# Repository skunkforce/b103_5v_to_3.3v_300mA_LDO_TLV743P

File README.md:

# edgy_board number b123
This design is part of the [edgy board project](https://github.com/skunkforce/edgy_boards). It provides a 3.3v 300mA LDO

# getting started
This repository uses submodules. After cloning use the command 

```$ git submodule update --init --recursive```

to pull the submodules before opening the project with kicad. 

# Tests
Tests can be found in [TESTS.md](TESTS.md)

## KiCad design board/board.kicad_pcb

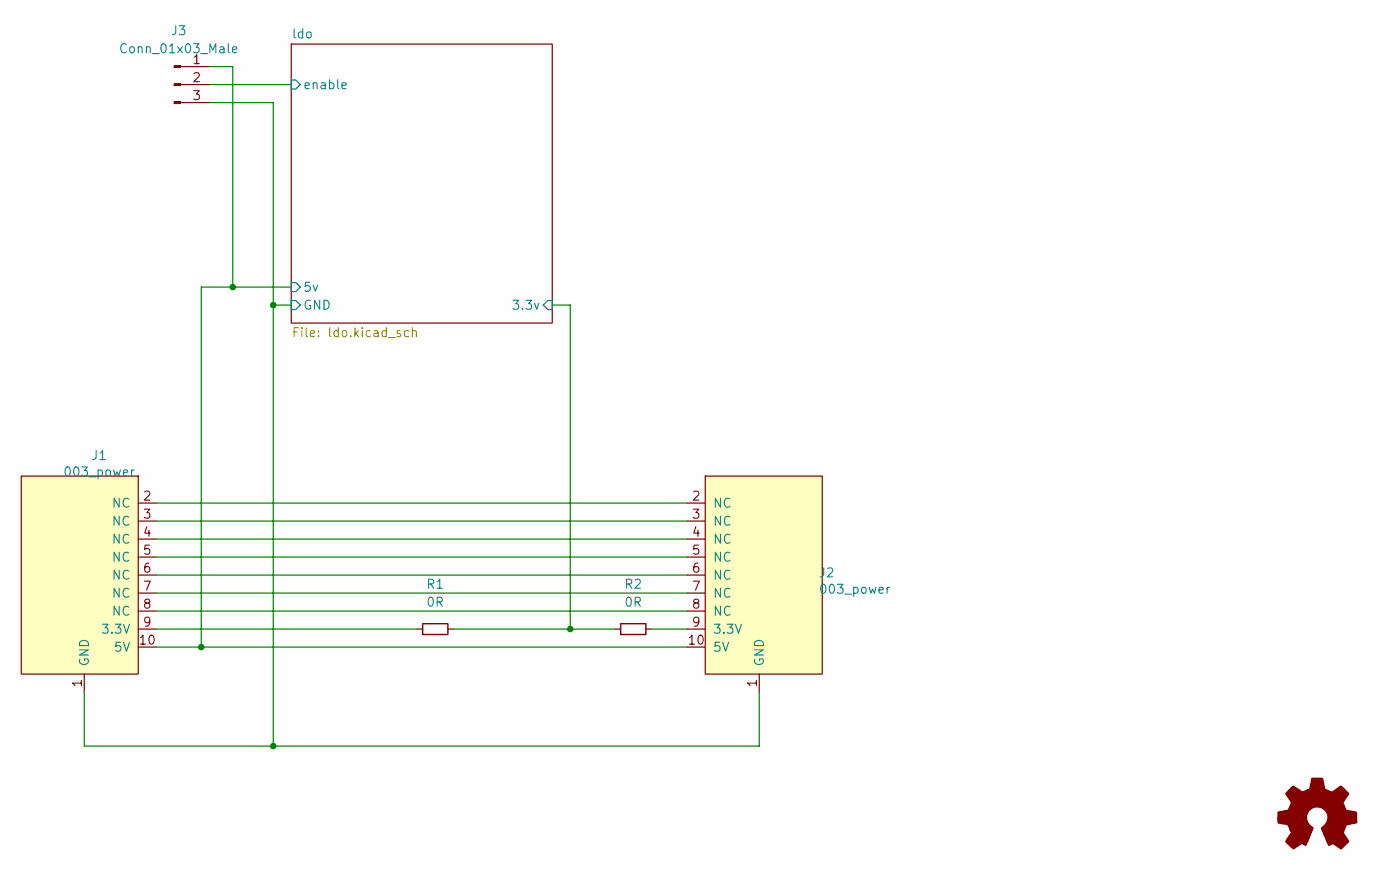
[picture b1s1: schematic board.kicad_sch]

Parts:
J1: 003_power; on_edge_2x05_device
J2: 003_power; on_edge_2x05_host
J3: Conn_01x03_Male; PinHeader_1x03_P2.54mm_Vertical
LOGO1: Logo_Open_Hardware_Small; OSHW-Symbol_6.7x6mm_SilkScreen
R1, R2: 0R; R_0603_1608Metric

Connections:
/ldo/3.3v: R1.2, R2.1; also elsewhere on the board
/ldo/5v: J1.10 (5V), J2.10 (5V), J3.1; also elsewhere on the board
/ldo/GND: J1.1 (GND), J2.1 (GND), J3.3; also elsewhere on the board
/ldo/enable: J3.2; also elsewhere on the board
unnamed: J1.9 (3.3V), R1.1
unnamed: J1.2 (NC), J2.2 (NC)
unnamed: J1.3 (NC), J2.3 (NC)
unnamed: J1.4 (NC), J2.4 (NC)
unnamed: J1.5 (NC), J2.5 (NC)
unnamed: J1.6 (NC), J2.6 (NC)
unnamed: J1.7 (NC), J2.7 (NC)
unnamed: J1.8 (NC), J2.8 (NC)
unnamed: J2.9 (3.3V), R2.2

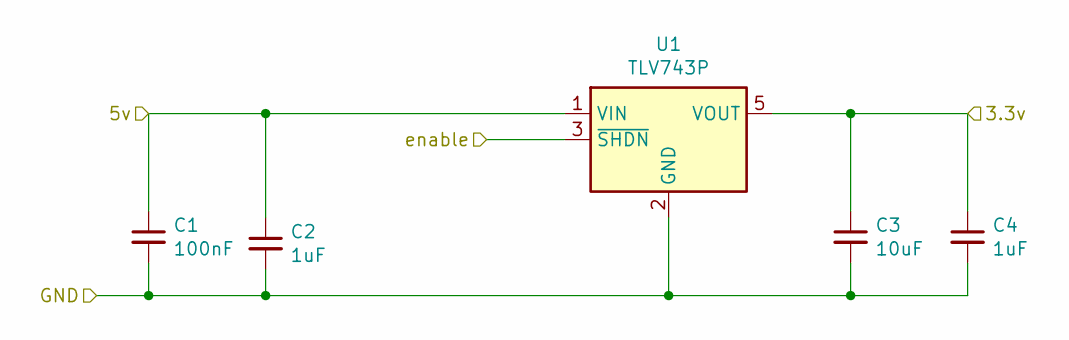
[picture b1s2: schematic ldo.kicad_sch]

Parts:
C1: 100nF; C_0603_1608Metric
C2, C4: 1uF; C_0603_1608Metric
C3: 10uF; C_0603_1608Metric
U1: TLV743P; SOT-23-5; MPN TLV74333PDBVR; Digi-Key_PN 296-47852-1-ND

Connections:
/ldo/3.3v: C3.1, C4.1, U1.5 (VOUT); also elsewhere on the board
/ldo/5v: C1.1, C2.1, U1.1 (VIN); also elsewhere on the board
/ldo/GND: C1.2, C2.2, C3.2, C4.2, U1.2 (GND); also elsewhere on the board
/ldo/enable: U1.3 (~SHDN); also elsewhere on the board

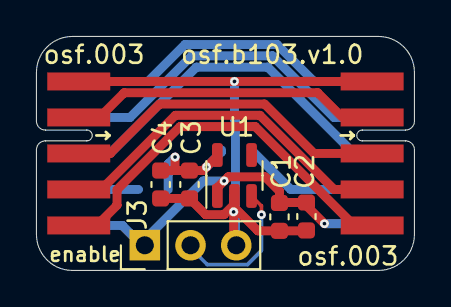
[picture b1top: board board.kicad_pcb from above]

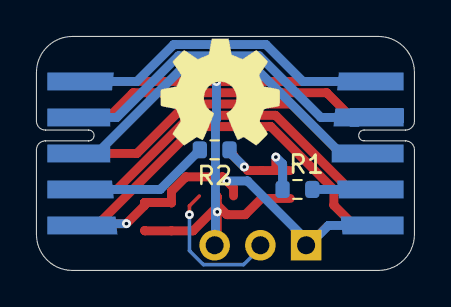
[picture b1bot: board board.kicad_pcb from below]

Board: 2 copper layers, 21.0 x 13.0 mm, 11 parts (3 on the bottom side), 13 nets.

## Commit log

2023-03-04 initial
2023-10-24 modernized layout to use 000 generic power symbols. the layout and thereofore the hardware version number is unaffected
